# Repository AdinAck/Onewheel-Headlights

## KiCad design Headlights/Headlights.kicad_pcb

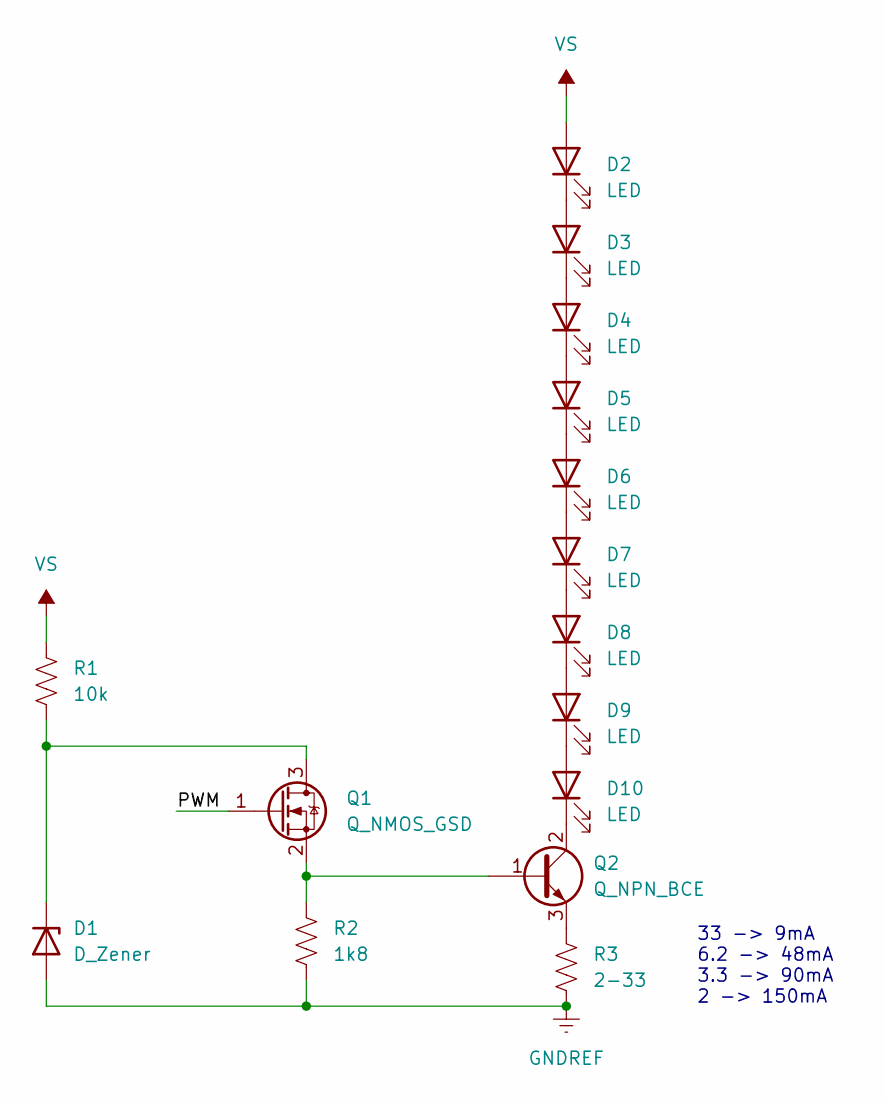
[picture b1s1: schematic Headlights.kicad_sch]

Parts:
D1: D_Zener; SOT-23; Part ADR510ARTZ-REEL7
D2, D3, D4, D5, D6, D7, D8, D9, D10: LED; LED_5050; Part L150-40905006000S0
Q1: Q_NMOS_GSD; SOT-23; Part PMV65UNER
Q2: Q_NPN_BCE; TO-252-2; Part MJD41CJ
R1: 10k; R_0603_1608Metric; Part ERJ-3EKF1002V
R2: 1k8; R_0603_1608Metric; Part ERJ-3EKF1801V
R3: 2-33; R_1210_3225Metric; Part ERJ-P14J330U, ERJ-P14J6R2U, ERJ-P14J3R3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

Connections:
/PWM: Q1.1 (G)
GNDREF: D1.2 (A), R2.2, R3.2
unnamed: D1.1 (K), Q1.3 (D), R1.2
unnamed: D2.1 (K), D3.2 (A)
unnamed: D3.1 (K), D4.2 (A)
unnamed: D4.1 (K), D5.2 (A)
unnamed: D5.1 (K), D6.2 (A)
unnamed: D6.1 (K), D7.2 (A)
unnamed: D7.1 (K), D8.2 (A)
unnamed: D8.1 (K), D9.2 (A)
unnamed: D9.1 (K), D10.2 (A)
unnamed: Q1.2 (S), Q2.1 (B), R2.1
unnamed: D10.1 (K), Q2.2 (C)
unnamed: Q2.3 (E), R3.1
VS: D2.2 (A), R1.1

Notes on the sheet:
33 -> 9mA 6.2 -> 48mA 3.3 -> 90mA 2 -> 150mA

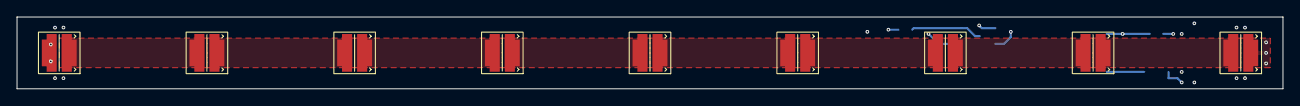
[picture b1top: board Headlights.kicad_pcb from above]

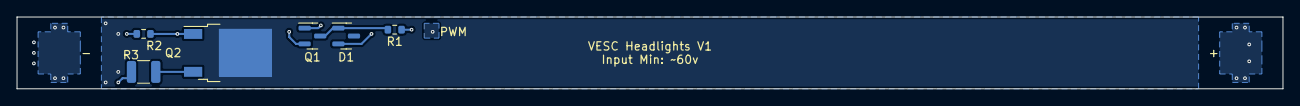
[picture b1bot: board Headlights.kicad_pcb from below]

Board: 4 copper layers, 152.4 x 8.6 mm, 15 parts (6 on the bottom side), 14 nets.

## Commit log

2023-01-18 4 layer
